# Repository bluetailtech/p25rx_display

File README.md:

# p25rx_display
Touch-lcd display for use with the P25RX receiver

Build Instructions (tested on a Debian system)

1) download GNU ARM Embedded Toolchain from here:
2) https://developer.arm.com/tools-and-software/open-source-software/developer-tools/gnu-toolchain/gnu-rm/downloads
3) The current firmare was compiled with version: 7-2018q2-update
4) Create a symbolic link to the compiler in the project directory:  'ln -s gcc-arm-none-eabi-7-2018-q2-update arm-toolchain'
5) Now you can compile the project from the project directory with:  'make'
6) Flip SW2 to the ON position before supplying power to the pcb. This will put the MCU into DFU programming mode.
7) Download the dfu-util software: http://dfu-util.sourceforge.net/
8) Program the device with dfu-util:   'dfu-util --device 0483:df11 -a 0 -s 0x08000000 -D build/p25rx_display_DFU.bin'
9) Return SW2 to the OFF position and cycle power.

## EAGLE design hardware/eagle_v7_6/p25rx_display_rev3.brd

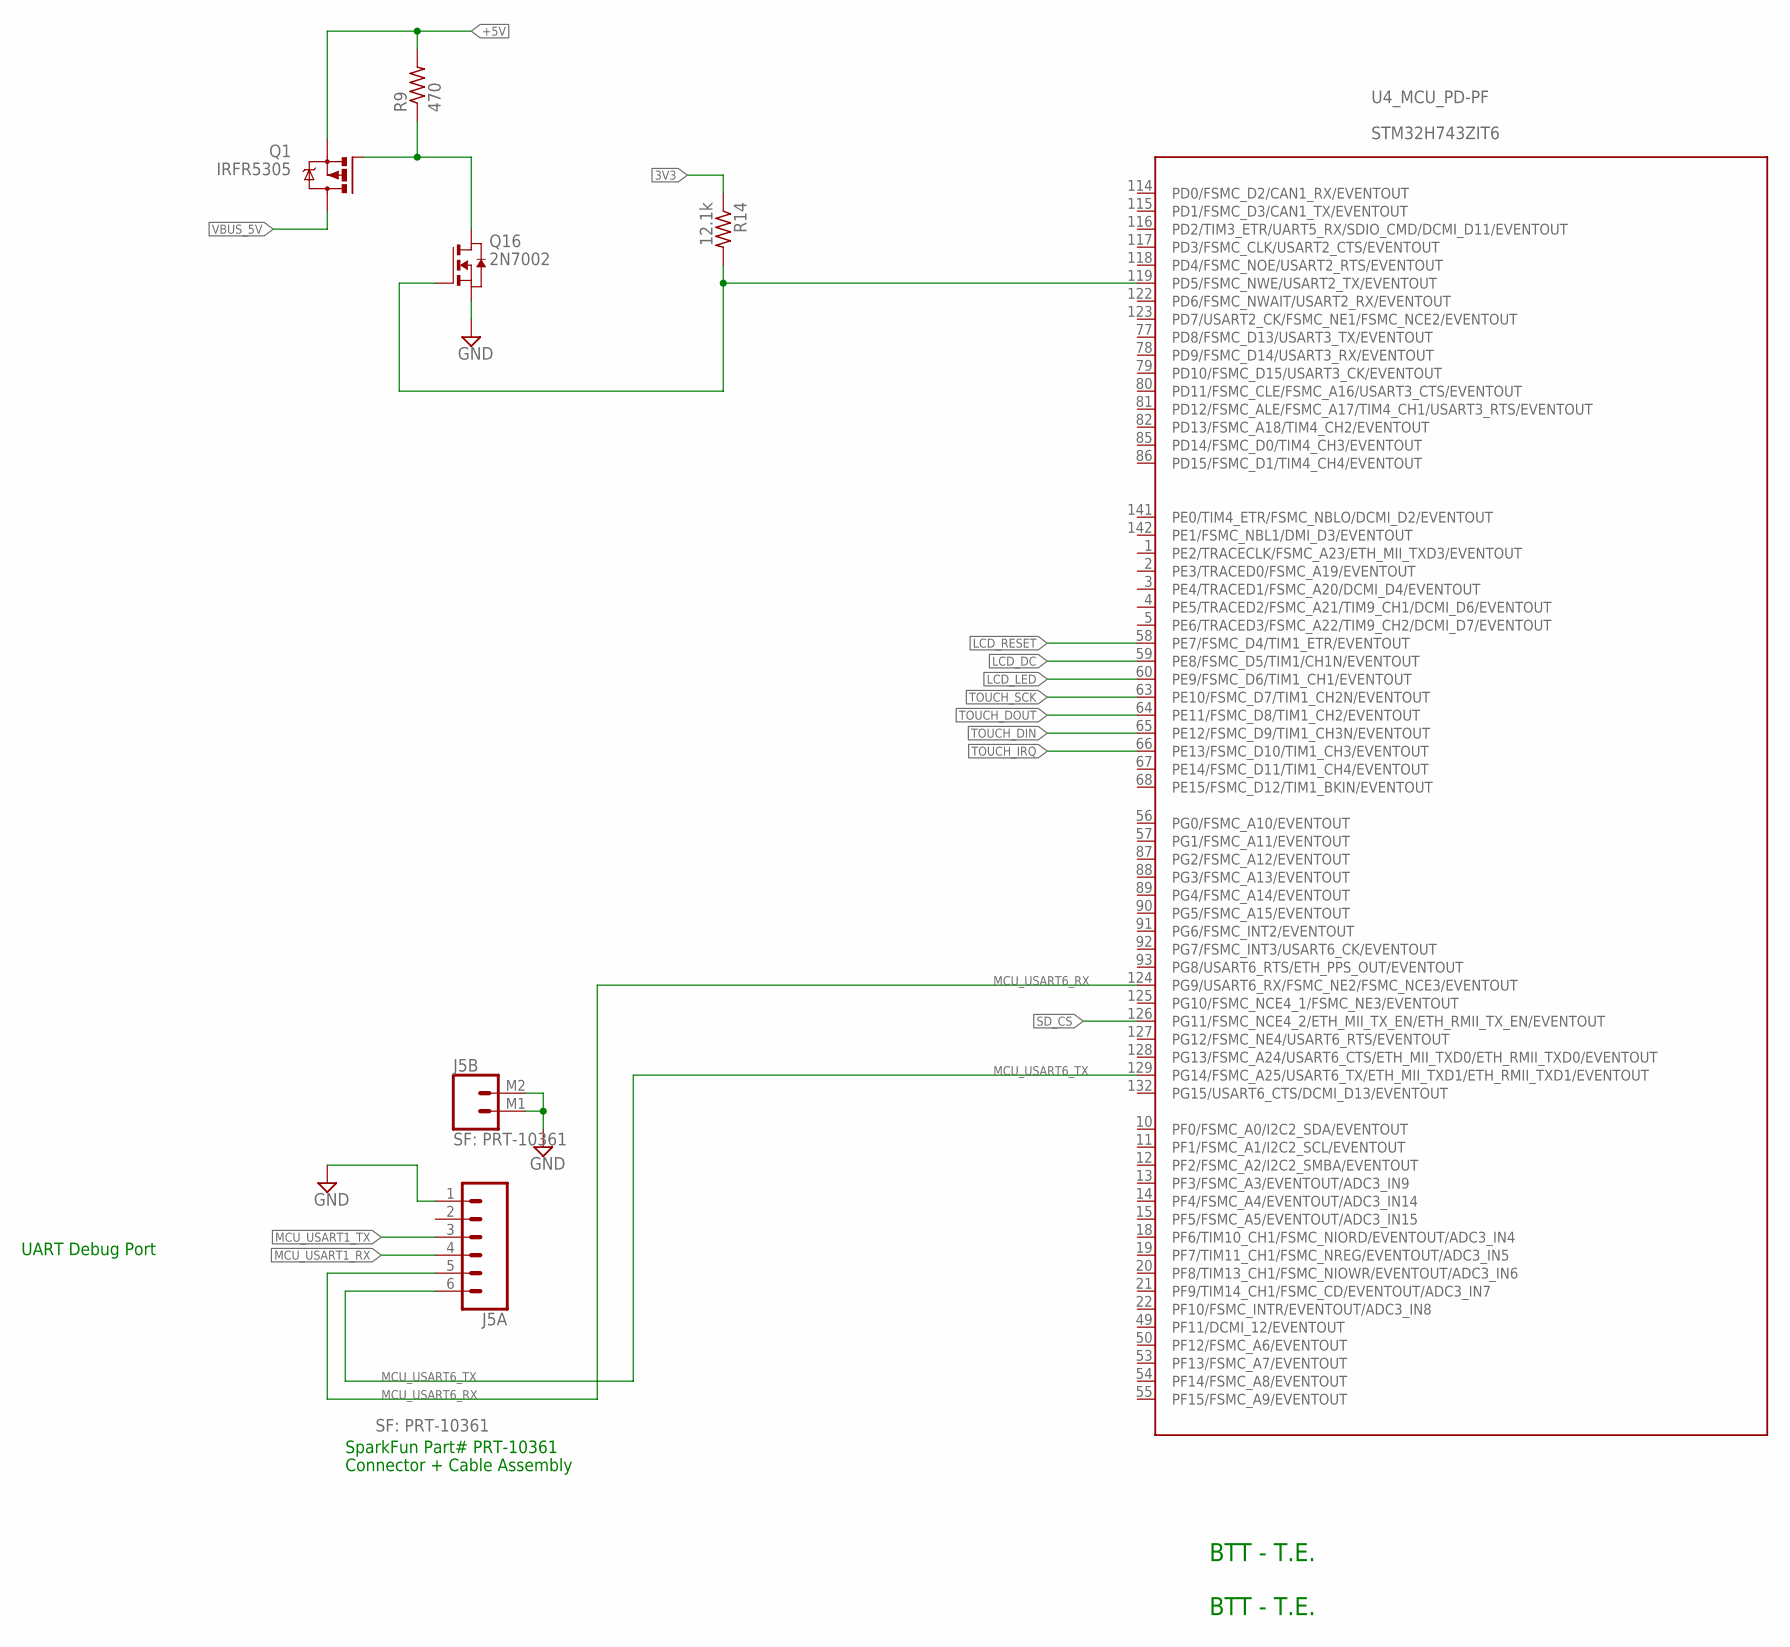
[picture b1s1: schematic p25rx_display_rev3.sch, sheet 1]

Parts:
J5: SF: PRT-10361; JST-6-SMD-HORI-1.0MM
Q1: IRFR5305; D-PAK_TO252AA
Q16: 2N7002; SOT23_2N7002_PACKAGE
R9: 470; R0603
R14: 12.1k; R0402
U4: STM32H743ZIT6; STM32F407_144

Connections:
3V3: R14.1; also elsewhere on the board
+5V: Q1.3 (S), R9.2; also elsewhere on the board
GND: J5.1, J5.M1 (1), J5.M2 (2), Q16.2 (S); also elsewhere on the board
LCD_DC: U4.59 (PE8/FSMC_D5/TIM1/CH1N/EVENTOUT); also elsewhere on the board
LCD_LED: U4.60 (PE9/FSMC_D6/TIM1_CH1/EVENTOUT); also elsewhere on the board
LCD_RESET: U4.58 (PE7/FSMC_D4/TIM1_ETR/EVENTOUT); also elsewhere on the board
MCU_USART1_RX: J5.4; also elsewhere on the board
MCU_USART1_TX: J5.3; also elsewhere on the board
MCU_USART6_RX: J5.5, U4.124 (PG9/USART6_RX/FSMC_NE2/FSMC_NCE3/EVENTO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)
MCU_USART6_TX: J5.6, U4.129 (PG14/FSMC_A25/USART6_TX/ETH_MII_TXD1/ET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)
unnamed: Q16.1 (G), R14.2, U4.119 (PD5/FSMC_NWE/USART2_TX/EVENTOUT)
unnamed: Q1.1 (G), Q16.3 (D), R9.1
SD_CS: U4.126 (PG11/FSMC_NCE4_2/ETH_MII_TX_EN/ETH_RMII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); also elsewhere on the board
TOUCH_DIN: U4.65 (PE12/FSMC_D9/TIM1_CH3N/EVENTOUT); also elsewhere on the board
TOUCH_DOUT: U4.64 (PE11/FSMC_D8/TIM1_CH2/EVENTOUT); also elsewhere on the board
TOUCH_IRQ: U4.66 (PE13/FSMC_D10/TIM1_CH3/EVENTOUT); also elsewhere on the board
TOUCH_SCK: U4.63 (PE10/FSMC_D7/TIM1_CH2N/EVENTOUT); also elsewhere on the board
VBUS_5V: Q1.4 (D); also elsewhere on the board

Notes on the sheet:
BTT - T.E.
UART Debug Port
SparkFun Part# PRT-10361
Connector + Cable Assembly

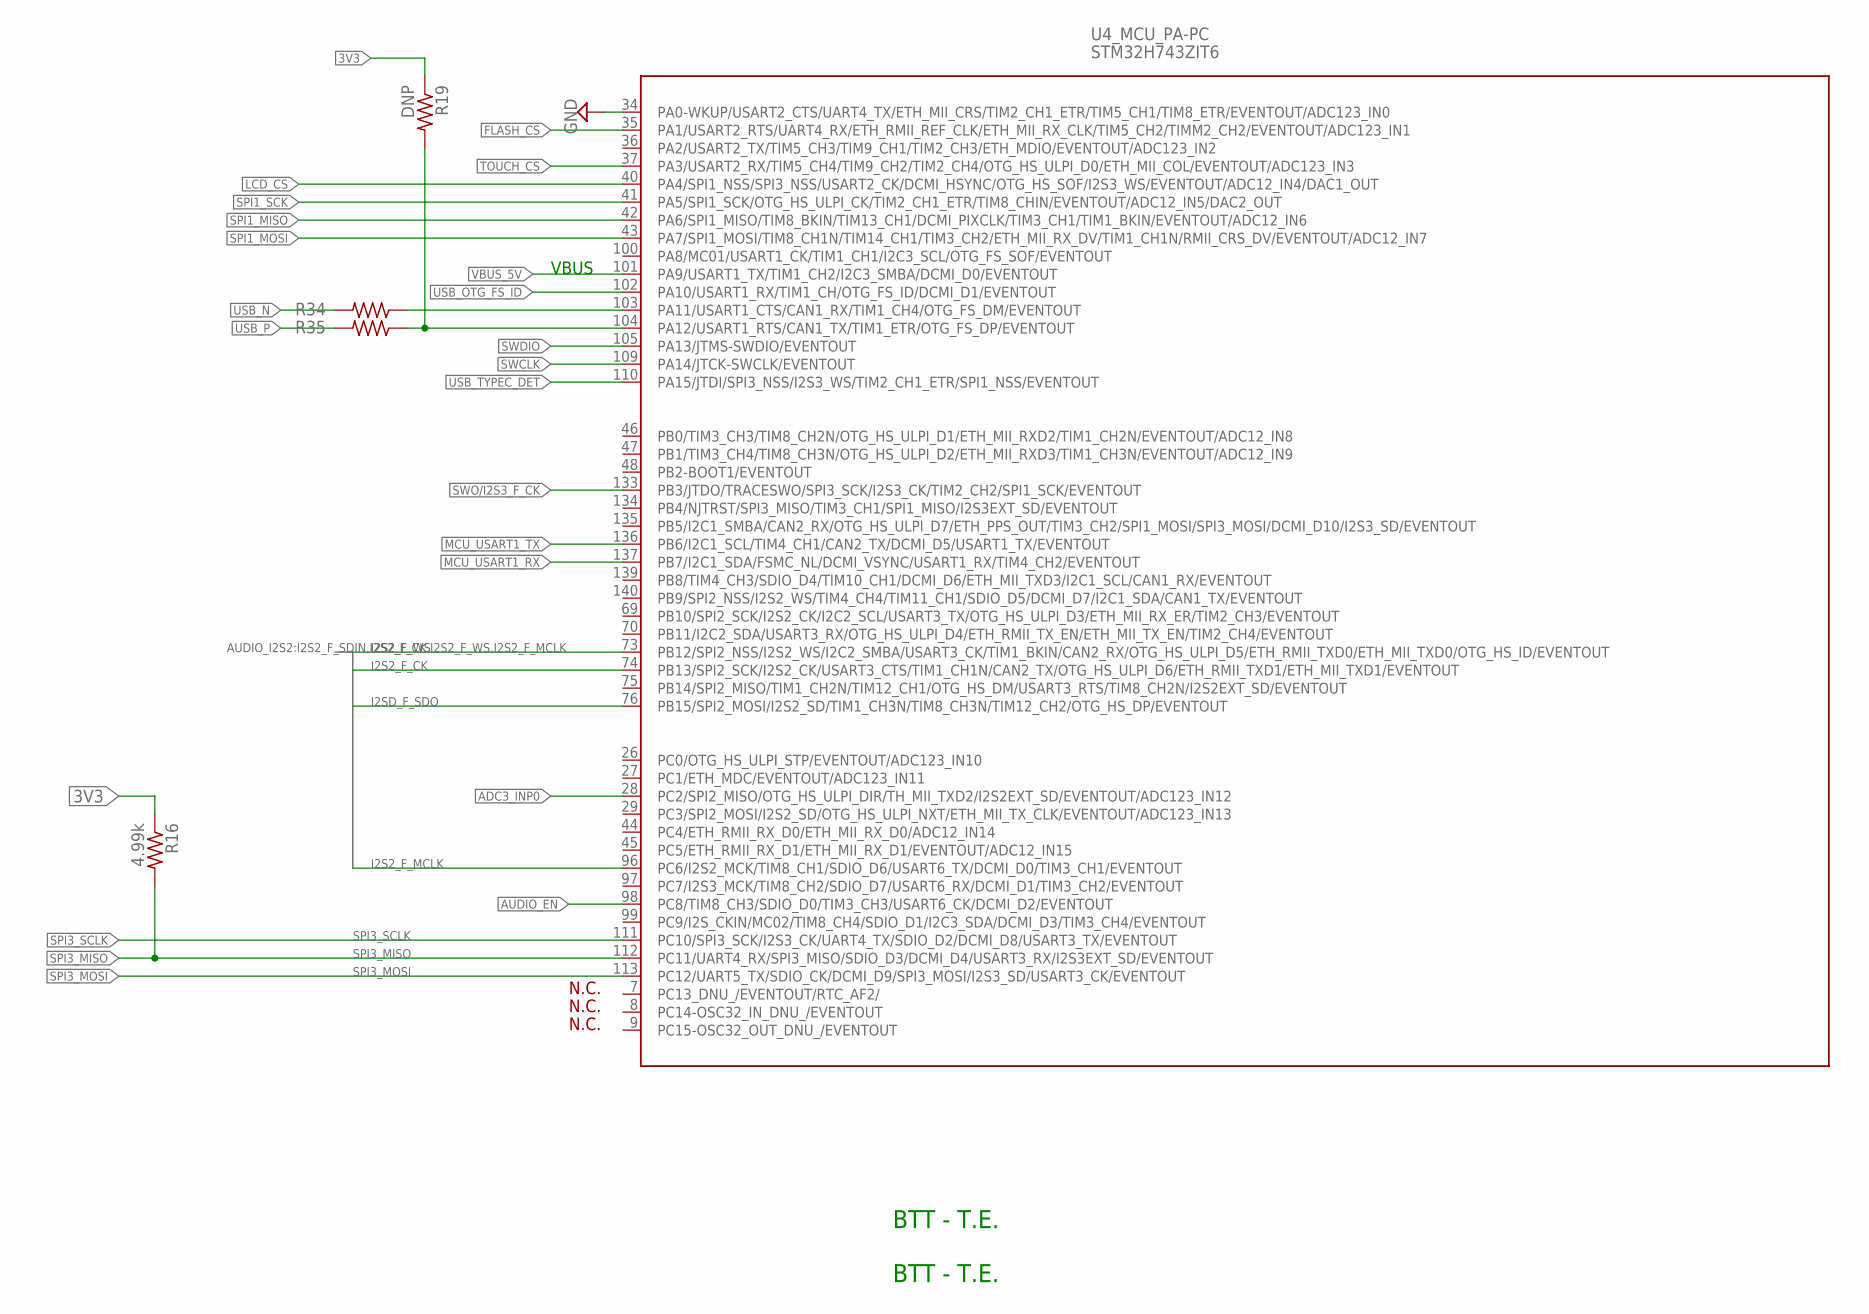
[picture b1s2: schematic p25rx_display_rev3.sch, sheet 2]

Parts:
R16: 4.99k; R0402
R19: DNP; R0603
R34, R35: 470; R0402
U4: STM32H743ZIT6; STM32F407_144

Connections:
3V3: R16.1, R19.1; also elsewhere on the board
ADC3_INP0: U4.28 (PC2/SPI2_MISO/OTG_HS_ULPI_DIR/TH_MII_TX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)
AUDIO_EN: U4.98 (PC8/TIM8_CH3/SDIO_D0/TIM3_CH3/USART6_CK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); also elsewhere on the board
FLASH_CS: U4.35 (PA1/USART2_RTS/UART4_RX/ETH_RMII_REF_CL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); also elsewhere on the board
GND: U4.34 (PA0-WKUP/USART2_CTS/UART4_TX/ETH_MII_CR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); also elsewhere on the board
I2S2_F_CK: U4.74 (PB13/SPI2_SCK/I2S2_CK/USART3_CTS/TIM1_C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); also elsewhere on the board
I2S2_F_MCLK: U4.96 (PC6/I2S2_MCK/TIM8_CH1/SDIO_D6/USART6_TX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); also elsewhere on the board
I2S2_F_WS: U4.73 (PB12/SPI2_NSS/I2S2_WS/I2C2_SMBA/USART3_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); also elsewhere on the board
I2SD_F_SDO: U4.76 (PB15/SPI2_MOSI/I2S2_SD/TIM1_CH3N/TIM8_C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); also elsewhere on the board
LCD_CS: U4.40 (PA4/SPI1_NSS/SPI3_NSS/USART2_CK/DCMI_HS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); also elsewhere on the board
MCU_USART1_RX: U4.137 (PB7/I2C1_SDA/FSMC_NL/DCMI_VSYNC/USART1_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); also elsewhere on the board
MCU_USART1_TX: U4.136 (PB6/I2C1_SCL/TIM4_CH1/CAN2_TX/DCMI_D5/U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); also elsewhere on the board
SPI1_MISO: U4.42 (PA6/SPI1_MISO/TIM8_BKIN/TIM13_CH1/DCMI_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); also elsewhere on the board
SPI1_MOSI: U4.43 (PA7/SPI1_MOSI/TIM8_CH1N/TIM14_CH1/TIM3_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); also elsewhere on the board
SPI1_SCK: U4.41 (PA5/SPI1_SCK/OTG_HS_ULPI_CK/TIM2_CH1_ET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); also elsewhere on the board
SPI3_MISO: R16.2, U4.112 (PC11/UART4_RX/SPI3_MISO/SDIO_D3/DCMI_D4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); also elsewhere on the board
SPI3_MOSI: U4.113 (PC12/UART5_TX/SDIO_CK/DCMI_D9/SPI3_MOSI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); also elsewhere on the board
SPI3_SCLK: U4.111 (PC10/SPI3_SCK/I2S3_CK/UART4_TX/SDIO_D2/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); also elsewhere on the board
SWCLK: U4.109 (PA14/JTCK-SWCLK/EVENTOUT); also elsewhere on the board
SWDIO: U4.105 (PA13/JTMS-SWDIO/EVENTOUT); also elsewhere on the board
SWO/I2S3_F_CK: U4.133 (PB3/JTDO/TRACESWO/SPI3_SCK/I2S3_CK/TIM2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); also elsewhere on the board
TOUCH_CS: U4.37 (PA3/USART2_RX/TIM5_CH4/TIM9_CH2/TIM2_CH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); also elsewhere on the board
USB_MCU_N: R34.1, U4.103 (PA11/USART1_CTS/CAN1_RX/TIM1_CH4/OTG_FS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)
USB_MCU_P: R19.2, R35.1, U4.104 (PA12/USART1_RTS/CAN1_TX/TIM1_ETR/OTG_FS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)
USB_N: R34.2; also elsewhere on the board
USB_OTG_FS_ID: U4.102 (PA10/USART1_RX/TIM1_CH/OTG_FS_ID/DCMI_D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); also elsewhere on the board
USB_P: R35.2; also elsewhere on the board
USB_TYPEC_DET: U4.110 (PA15/JTDI/SPI3_NSS/I2S3_WS/TIM2_CH1_ETR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); also elsewhere on the board
VBUS_5V: U4.101 (PA9/USART1_TX/TIM1_CH2/I2C3_SMBA/DCMI_D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); also elsewhere on the board

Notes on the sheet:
BTT - T.E.
VBUS

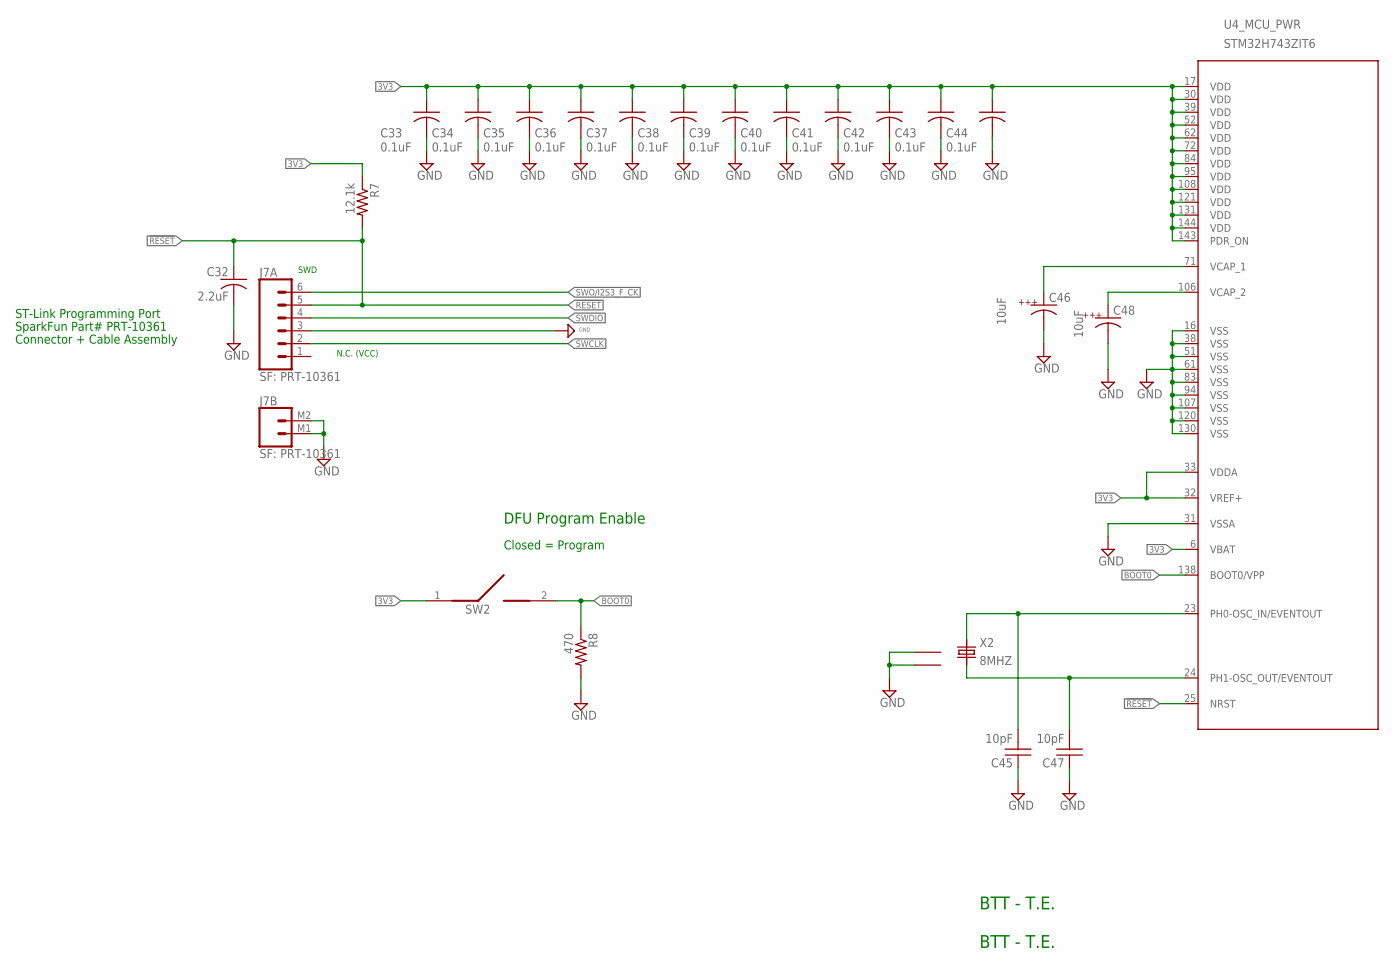
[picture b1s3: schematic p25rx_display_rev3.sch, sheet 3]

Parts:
C32: 2.2uF; C0805
C33, C34, C35, C36, C37, C38, C39, C40, C41, C42, C43, C44: 0.1uF; 0402
C45, C47: 10pF; C0603
C46, C48: 10uF; 1210K
J7: SF: PRT-10361; JST-6-SMD-HORI-1.0MM
R7: 12.1k; R0603
R8: 470; R0402
SW2: CHS-01TA; CHS1BIT
U4: STM32H743ZIT6; STM32F407_144
X2: 8MHZ; ECS-250-20-30B-DU_CRYSTAL

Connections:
3V3: C33.1 (A), C34.1 (A), C35.1 (A), C36.1 (A), C37.1 (A), C38.1 (A), C39.1 (A), C40.1 (A), C41.1 (A), C42.1 (A), C43.1 (A), C44.1 (A), R7.1, SW2.1, U4.6 (VBAT), U4.17 (VDD), U4.30 (VDD), U4.32 (VREF+), U4.33 (VDDA), U4.39 (VDD), U4.52 (VDD), U4.62 (VDD), U4.72 (VDD), U4.84 (VDD), U4.95 (VDD), U4.108 (VDD), U4.121 (VDD), U4.131 (VDD), U4.143 (PDR_ON), U4.144 (VDD); also elsewhere on the board
20MHZ_REF: C45.2, U4.23 (PH0-OSC_IN/EVENTOUT), X2.1
!RESET: C32.1, J7.5, R7.2, U4.25 (NRST)
BOOT0: R8.1, SW2.2, U4.138 (BOOT0/VPP)
GND: C32.2, C33.2 (C), C34.2 (C), C35.2 (C), C36.2 (C), C37.2 (C), C38.2 (C), C39.2 (C), C40.2 (C), C41.2 (C), C42.2 (C), C43.2 (C), C44.2 (C), C45.1, C46.C, C47.1, C48.C, J7.3, J7.M1 (1), J7.M2 (2), R8.2, U4.16 (VSS), U4.31 (VSSA), U4.38 (VSS), U4.51 (VSS), U4.61 (VSS), U4.83 (VSS), U4.94 (VSS), U4.107 (VSS), U4.120 (VSS), U4.130 (VSS), X2.GND@1 (1), X2.GND@2 (2); also elsewhere on the board
unnamed: C48.A, U4.106 (VCAP_2)
unnamed: C46.A, U4.71 (VCAP_1)
SWCLK: J7.2; also elsewhere on the board
SWDIO: J7.4; also elsewhere on the board
SWO/I2S3_F_CK: J7.6; also elsewhere on the board
X2: C47.2, U4.24 (PH1-OSC_OUT/EVENTOUT), X2.3

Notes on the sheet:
BTT - T.E.
SWD
N.C. (VCC)
DFU Program Enable
Closed = Program
ST-Link Programming Port
SparkFun Part# PRT-10361
Connector + Cable Assembly

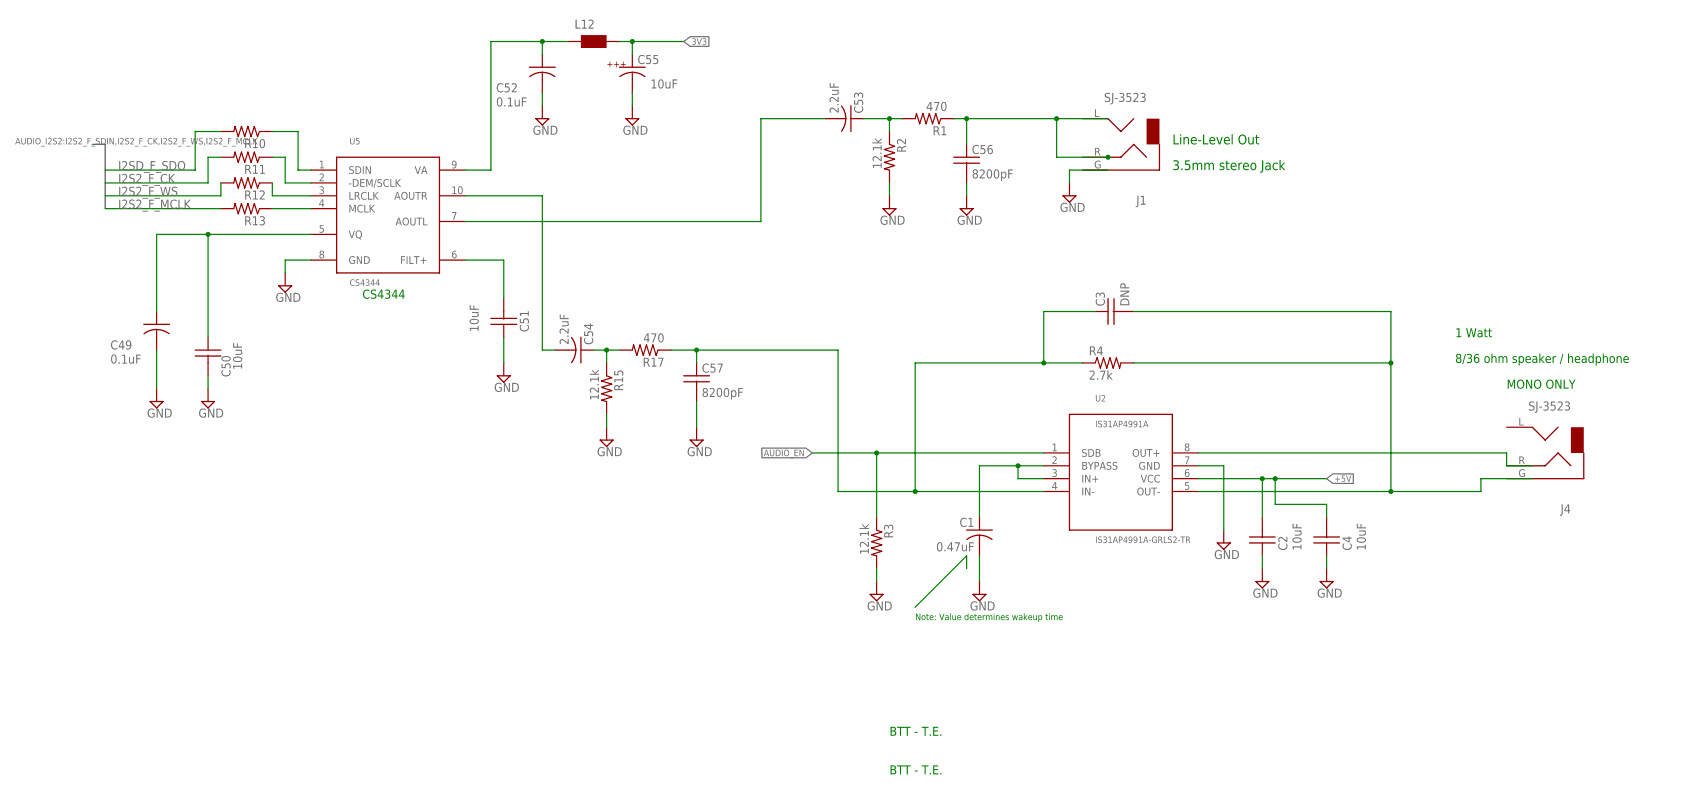
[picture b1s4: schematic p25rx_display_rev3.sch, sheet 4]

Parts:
C1: 0.47uF; C0805
C2, C4, C50, C51: 10uF; C0805
C3: DNP; C0603
C49, C52: 0.1uF; 0402
C53, C54: 2.2uF; C0805
C55: 10uF; 1210K
C56, C57: 8200pF; C0603
J1, J4: SJ-3523
L12: WE-CBF_0603; 0603
R1, R10, R11, R12, R13, R17: 470; R0402
R2, R3, R15: 12.1k; R0603
R4: 2.7k; R0603
U2: IS31AP4991A-GRLS2-TR; SO8
U5: CS4344; MSOP10

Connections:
3V3: C55.A, L12.2; also elsewhere on the board
+5V: C2.2, C4.2, U2.6 (VCC); also elsewhere on the board
AUDIO_EN: R3.1, U2.1 (SDB); also elsewhere on the board
AUDIO_LEFT: C56.1, J1.L, J1.R, R1.1
AUDIO_RIGHT: C3.1, C57.1, R4.1, R17.1, U2.4 (IN-)
GND: C1.2, C2.1, C4.1, C49.2 (C), C50.2, C51.1, C52.2 (C), C55.C, C56.2, C57.2, J1.G, R2.2, R3.2, R15.2, U2.7 (GND), U5.8 (GND); also elsewhere on the board
I2S2_F_CK: R11.2; also elsewhere on the board
I2S2_F_MCLK: R13.2; also elsewhere on the board
I2S2_F_WS: R12.2; also elsewhere on the board
I2SD_F_SDO: R10.2; also elsewhere on the board
unnamed: J4.R, U2.8 (OUT+)
unnamed: C1.1, U2.2 (BYPASS), U2.3 (IN+)
unnamed: C3.2, J4.G, R4.2, U2.5 (OUT-)
unnamed: C53.2, U5.7 (AOUTL)
unnamed: C54.2, U5.10 (AOUTR)
unnamed: R13.1, U5.4 (MCLK)
unnamed: R12.1, U5.3 (LRCLK)
unnamed: R11.1, U5.2 (-DEM/SCLK)
unnamed: R10.1, U5.1 (SDIN)
unnamed: C51.2, U5.6 (FILT+)
unnamed: C49.1 (A), C50.1, U5.5 (VQ)
unnamed: C53.1, R1.2, R2.1
unnamed: C54.1, R15.1, R17.2
unnamed: C52.1 (A), L12.1, U5.9 (VA)

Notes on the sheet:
BTT - T.E.
CS4344
Line-Level Out
3.5mm stereo Jack
Note: Value determines wakeup time
MONO ONLY
8/36 ohm speaker / headphone
1 Watt

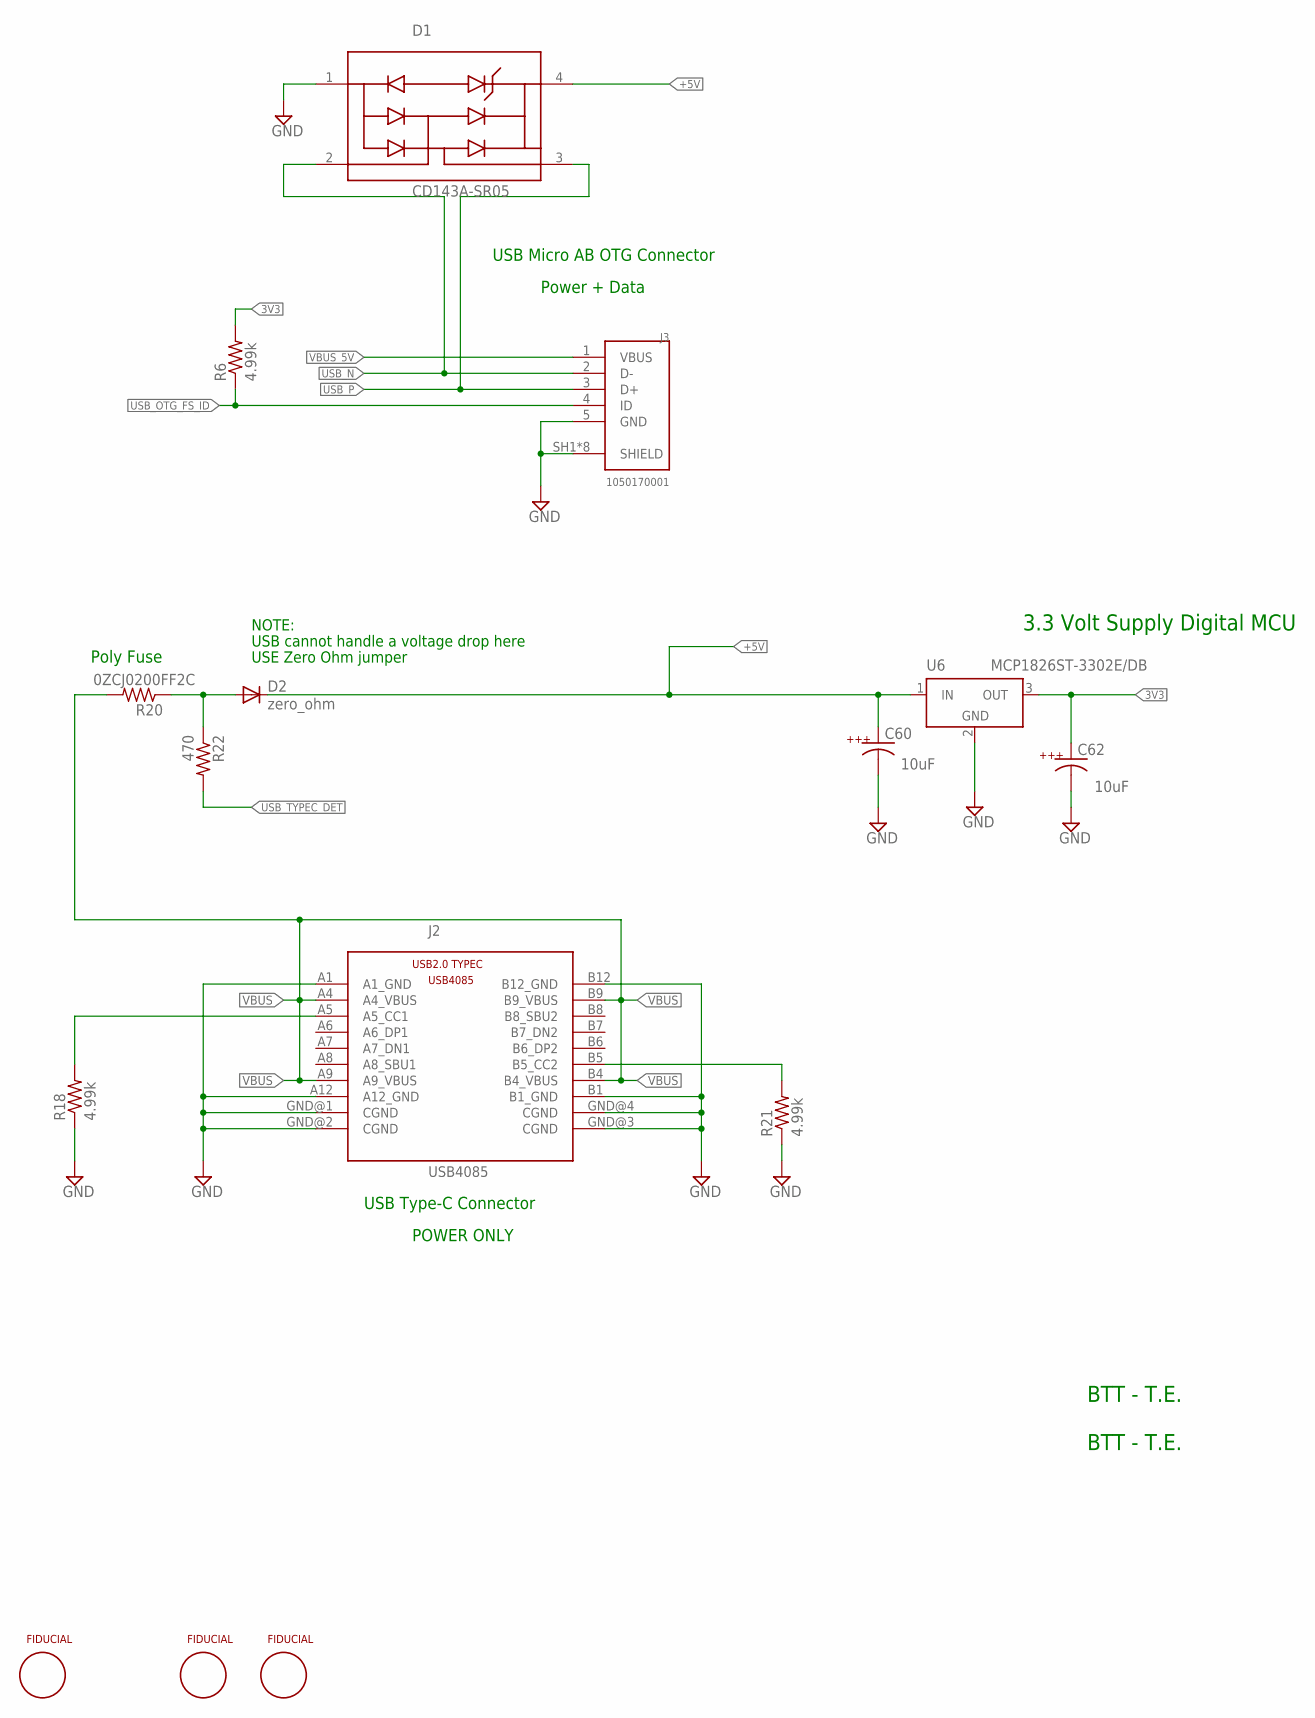
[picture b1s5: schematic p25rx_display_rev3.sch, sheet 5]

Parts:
C60, C62: 10uF; 1210K
D1: CD143A-SR05; SR2.8.TCT_1PRIMARY
D2: zero_ohm; SMB
FID1, FID3, FID4: FIDUCIALSMD; FIDUCIAL
J2: USB4085; GCT_PN_USB4085
J3: 1050170001; MOLEX_1050170001
R6, R18, R21: 4.99k; R0402
R20: 0ZCJ0200FF2C; R1206
R22: 470; R0402
U6: MCP1826ST-3302E/DB; SOT223

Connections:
3V3: C62.A, R6.2, U6.3 (OUT); also elsewhere on the board
+5V: C60.A, D1.4 (REF), D2.C, U6.1 (IN); also elsewhere on the board
GND: C60.C, C62.C, D1.1 (GND), J2.A1 (A1_GND), J2.A12 (A12_GND), J2.B1 (B1_GND), J2.B12 (B12_GND), J2.GND@1 (CGND), J2.GND@2 (CGND), J2.GND@3 (CGND), J2.GND@4 (CGND), J3.5 (GND), J3.SH1 (SHIELD), J3.SH2 (SHIELD), J3.SH3 (SHIELD), J3.SH4 (SHIELD), J3.SH5 (SHIELD), J3.SH6 (SHIELD), J3.SH7 (SHIELD), J3.SH8 (SHIELD), R18.1, R21.1, U6.2 (GND), U6.4 (GND); also elsewhere on the board
unnamed: D2.A, R20.1, R22.1
unnamed: J2.B5 (B5_CC2), R21.2
unnamed: J2.A5 (A5_CC1), R18.2
USB_N: D1.2 (I/O), J3.2 (D-); also elsewhere on the board
USB_OTG_FS_ID: J3.4 (ID), R6.1; also elsewhere on the board
USB_P: D1.3 (I/O), J3.3 (D+); also elsewhere on the board
USB_TYPEC_DET: R22.2; also elsewhere on the board
VBUS: J2.A4 (A4_VBUS), J2.A9 (A9_VBUS), J2.B4 (B4_VBUS), J2.B9 (B9_VBUS), R20.2
VBUS_5V: J3.1 (VBUS); also elsewhere on the board

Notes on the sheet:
BTT - T.E.
3.3 Volt Supply Digital MCU
USB Type-C Connector
POWER ONLY
Poly Fuse
USB Micro AB OTG Connector
Power + Data
USB cannot handle a voltage drop here
USE Zero Ohm jumper
NOTE:

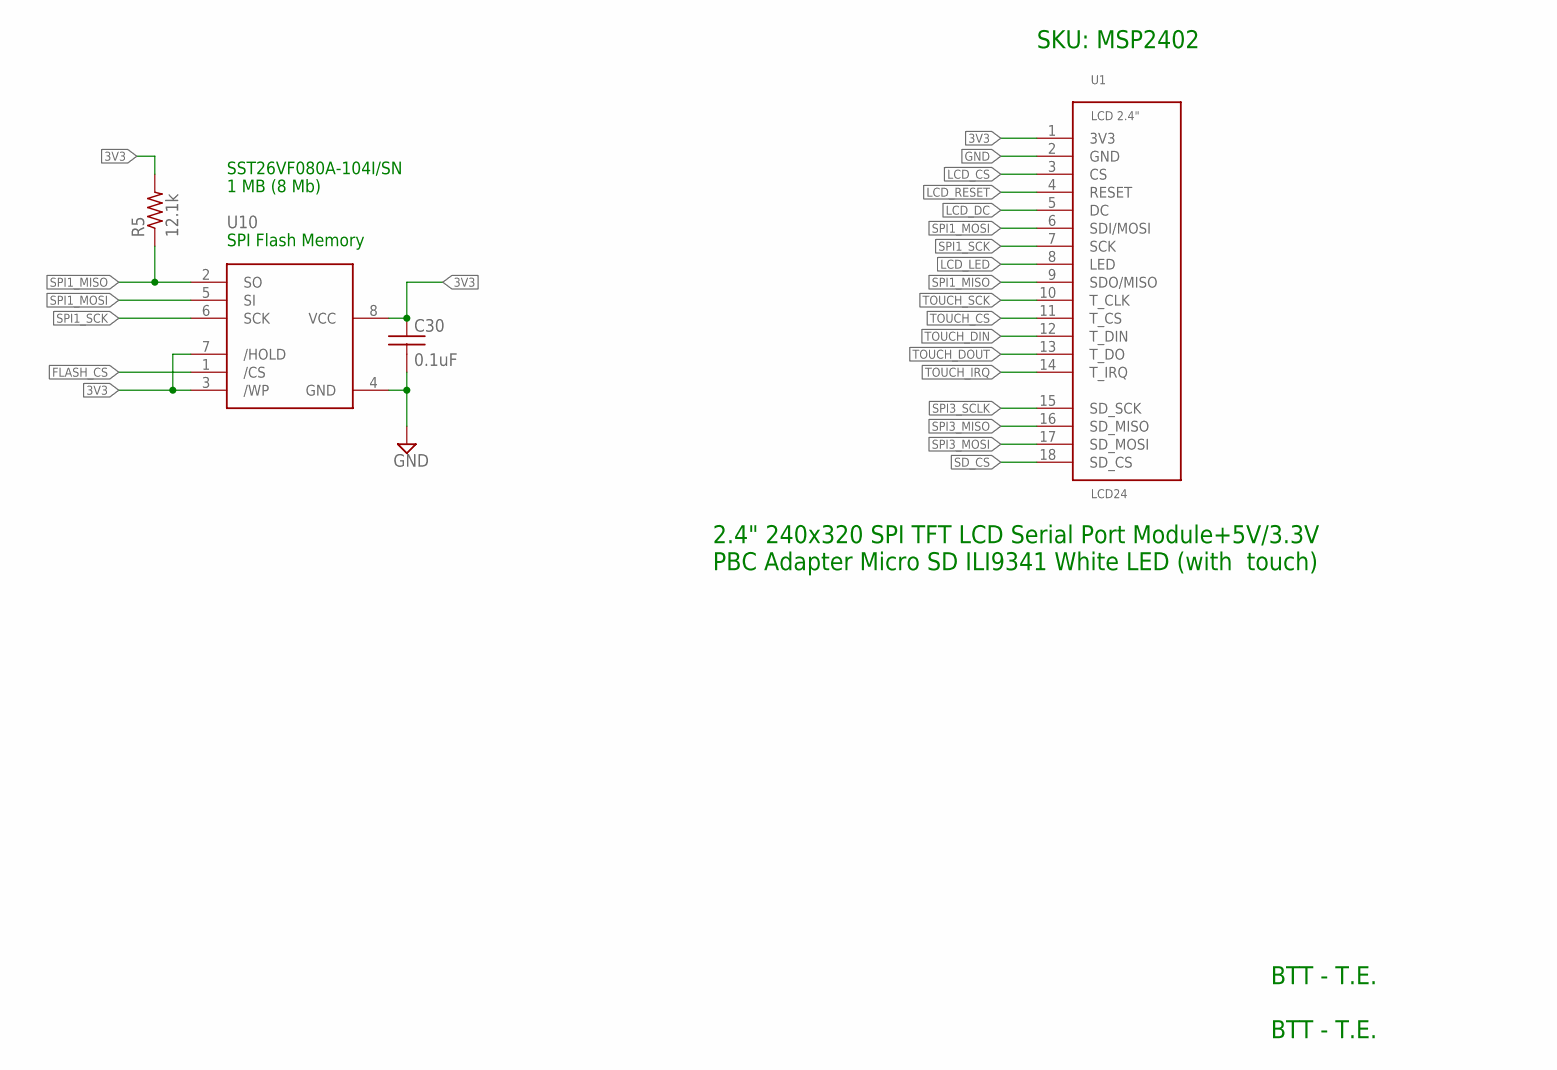
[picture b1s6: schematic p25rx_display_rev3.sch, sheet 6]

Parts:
C30: 0.1uF; C0402
R5: 12.1k; R0603
U1: LCD24; LCD_24
U10: AT25F512ASOIC; SO8

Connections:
3V3: C30.1, R5.2, U1.1 (3V3), U10.3 (/WP), U10.7 (/HOLD), U10.8 (VCC); also elsewhere on the board
FLASH_CS: U10.1 (/CS); also elsewhere on the board
GND: C30.2, U1.2 (GND), U10.4 (GND); also elsewhere on the board
LCD_CS: U1.3 (CS); also elsewhere on the board
LCD_DC: U1.5 (DC); also elsewhere on the board
LCD_LED: U1.8 (LED); also elsewhere on the board
LCD_RESET: U1.4 (RESET); also elsewhere on the board
SD_CS: U1.18 (SD_CS); also elsewhere on the board
SPI1_MISO: R5.1, U1.9 (SDO/MISO), U10.2 (SO); also elsewhere on the board
SPI1_MOSI: U1.6 (SDI/MOSI), U10.5 (SI); also elsewhere on the board
SPI1_SCK: U1.7 (SCK), U10.6 (SCK); also elsewhere on the board
SPI3_MISO: U1.16 (SD_MISO); also elsewhere on the board
SPI3_MOSI: U1.17 (SD_MOSI); also elsewhere on the board
SPI3_SCLK: U1.15 (SD_SCK); also elsewhere on the board
TOUCH_CS: U1.11 (T_CS); also elsewhere on the board
TOUCH_DIN: U1.12 (T_DIN); also elsewhere on the board
TOUCH_DOUT: U1.13 (T_DO); also elsewhere on the board
TOUCH_IRQ: U1.14 (T_IRQ); also elsewhere on the board
TOUCH_SCK: U1.10 (T_CLK); also elsewhere on the board

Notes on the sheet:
BTT - T.E.
SPI Flash Memory
SKU: MSP2402
2.4" 240x320 SPI TFT LCD Serial Port Module+5V/3.3V PBC Adapter Micro SD ILI9341 White LED (with touch)
SST26VF080A-104I/SN
1 MB (8 Mb)

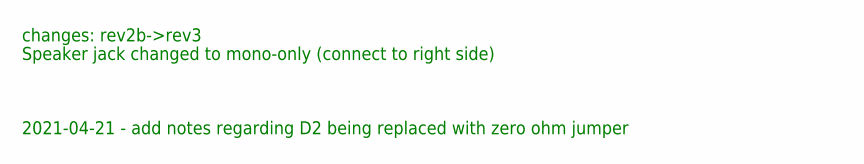
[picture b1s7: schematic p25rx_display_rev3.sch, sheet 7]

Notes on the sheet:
changes: rev2b->rev3
Speaker jack changed to mono-only (connect to right side)
2021-04-21 - add notes regarding D2 being replaced with zero ohm jumper

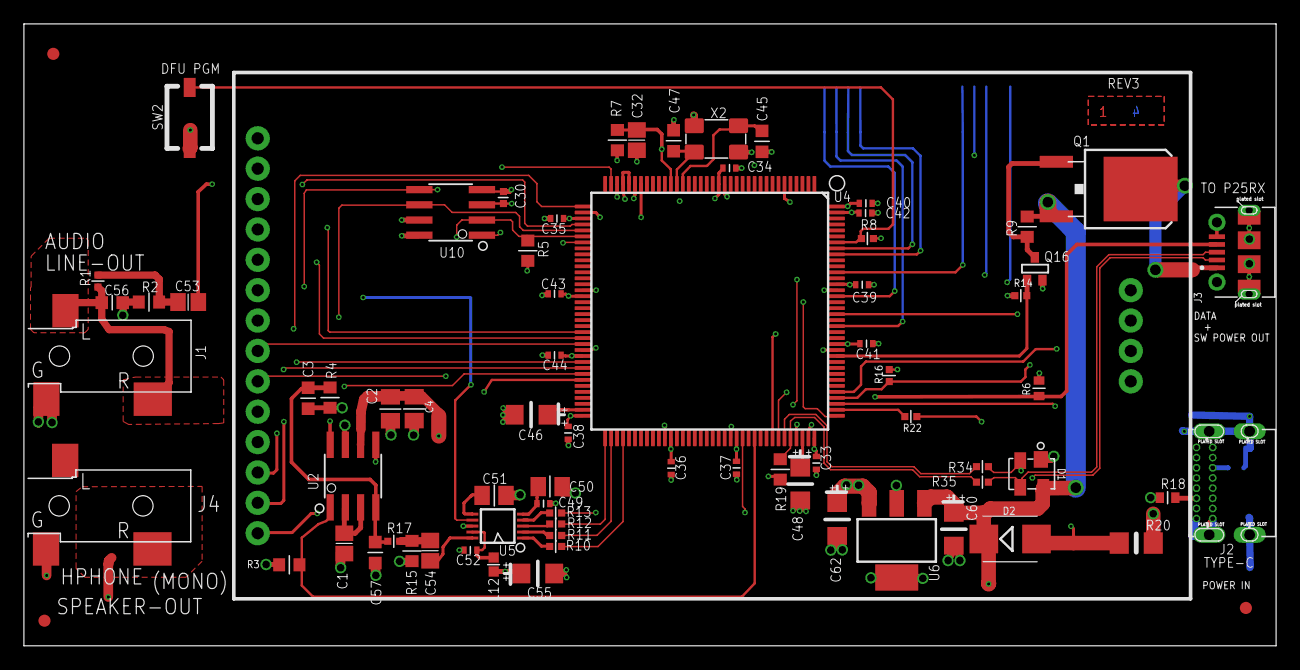
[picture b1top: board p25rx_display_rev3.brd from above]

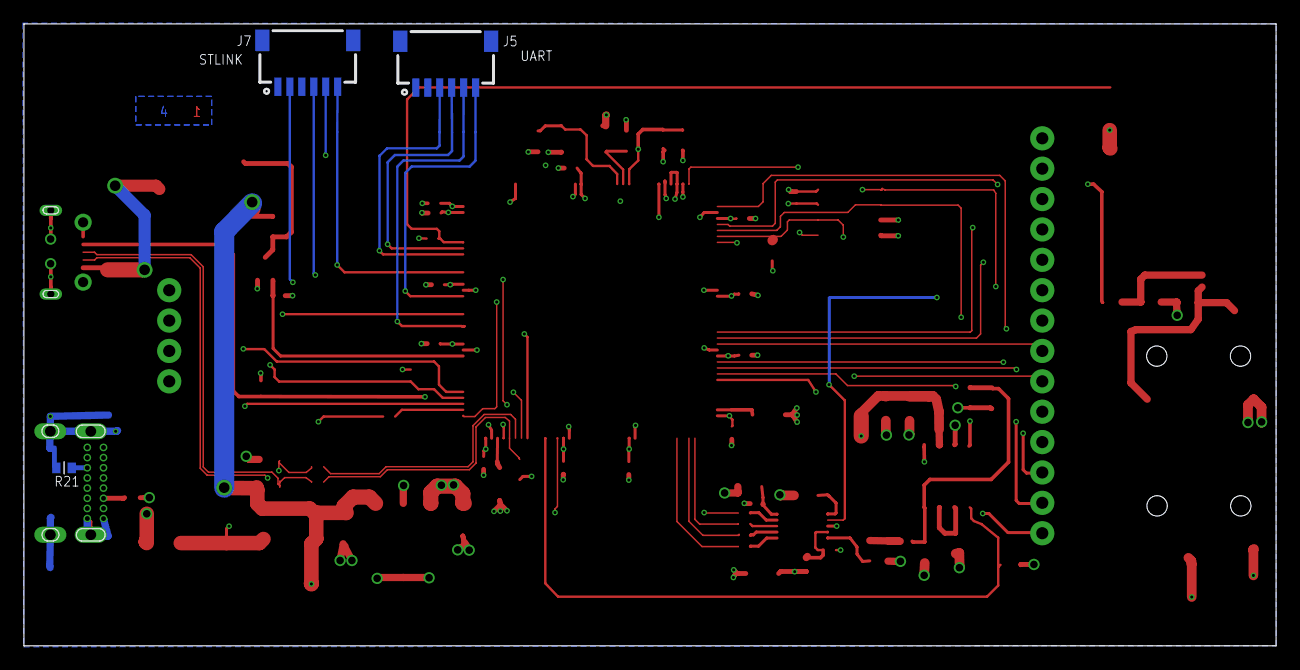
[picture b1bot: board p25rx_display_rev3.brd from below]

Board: 4 copper layers, 104.7 x 52.0 mm, 79 parts (3 on the bottom side), 67 nets.

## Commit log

2021-02-28 added eagle files
2021-02-28 add pdf schematic
2021-04-15 fix issues with usb connectivity between display<>p25rx on power-up
2021-04-15 more updates to usb init
2021-04-15 2021-04-15_1214 more reliable usb startup
2021-04-15 release 2021-04-15_1530 make usb init more reliable
2021-04-15 2021-04-15_1554 fix issue with talk group hold button
2021-04-15 2021-04-15_1632 usb init much more reliable now. add some delay between command tx
2021-04-15 2021-04-15_1653 usb_tick being called to often
2021-04-16 2021-04-15_1722 more reliable usb
2021-04-16 2021-04-15_1743
2021-04-16 2021-04-15_2056 add connecting message to display on startup
2021-04-16 2021-04-15_2130 add call to usb_restart() back in
2021-04-16 2021-04-16_0303 update sys_id on page1 display when roaming
2021-04-21 slow IQ plot drawing to free up more I/O bw
2021-04-21 update notes on schematic regarding D2
2021-04-29 increase startup delay to get some new displays USB working with all tested P25RX devices
2021-05-02 add openocd programming related information
2021-05-02 fix example openocd telnet command example

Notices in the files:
parts and their libraries:
cirrus-3: Copyright (C) 2005 by Bob Starr, rtzaudio@mindspring.com
SparkFun-Connectors: Licensing: Creative Commons ShareAlike 4.0 International - https://creativecommons.org/licenses/by-sa/4.0
